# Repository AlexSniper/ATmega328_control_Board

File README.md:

# ATmega328 Control Board

Custom embedded control board based on the ATmega328PU microcontroller, designed in KiCad and compatible with Arduino firmware.

## Prototype Board

## Assembly

## Testing Setup

## Clock Verification
External 16 MHz crystal verified using oscilloscope.

## Power Testing
Board powered and tested using laboratory power supply.

## LCD Interface Test
16×2 LCD connected to the ATmega328 board to verify digital IO functionality and firmware operation.
Display output confirms correct microcontroller operation.

.png)

### Features
- ATmega328PU microcontroller
- 16 MHz external crystal
- MOSFET output drivers
- Screw terminal IO
- USB programming interface
- External power supply

## Repository structure

hardware – KiCad PCB design  
firmware – Arduino firmware  
gerbers – manufacturing files  
bom – bill of materials  
docs – schematic PDF  
images – hardware prototype photos

## Hardware validation

Clock oscillator verified with oscilloscope.

Board powered and tested using laboratory power supply.

## Hardware Revision History

v0.1 – Initial prototype PCB  
v0.2 – Improved routing and component placement  
v0.3 – Stable prototype, validated clock and power supply

## Author

AL Robotics

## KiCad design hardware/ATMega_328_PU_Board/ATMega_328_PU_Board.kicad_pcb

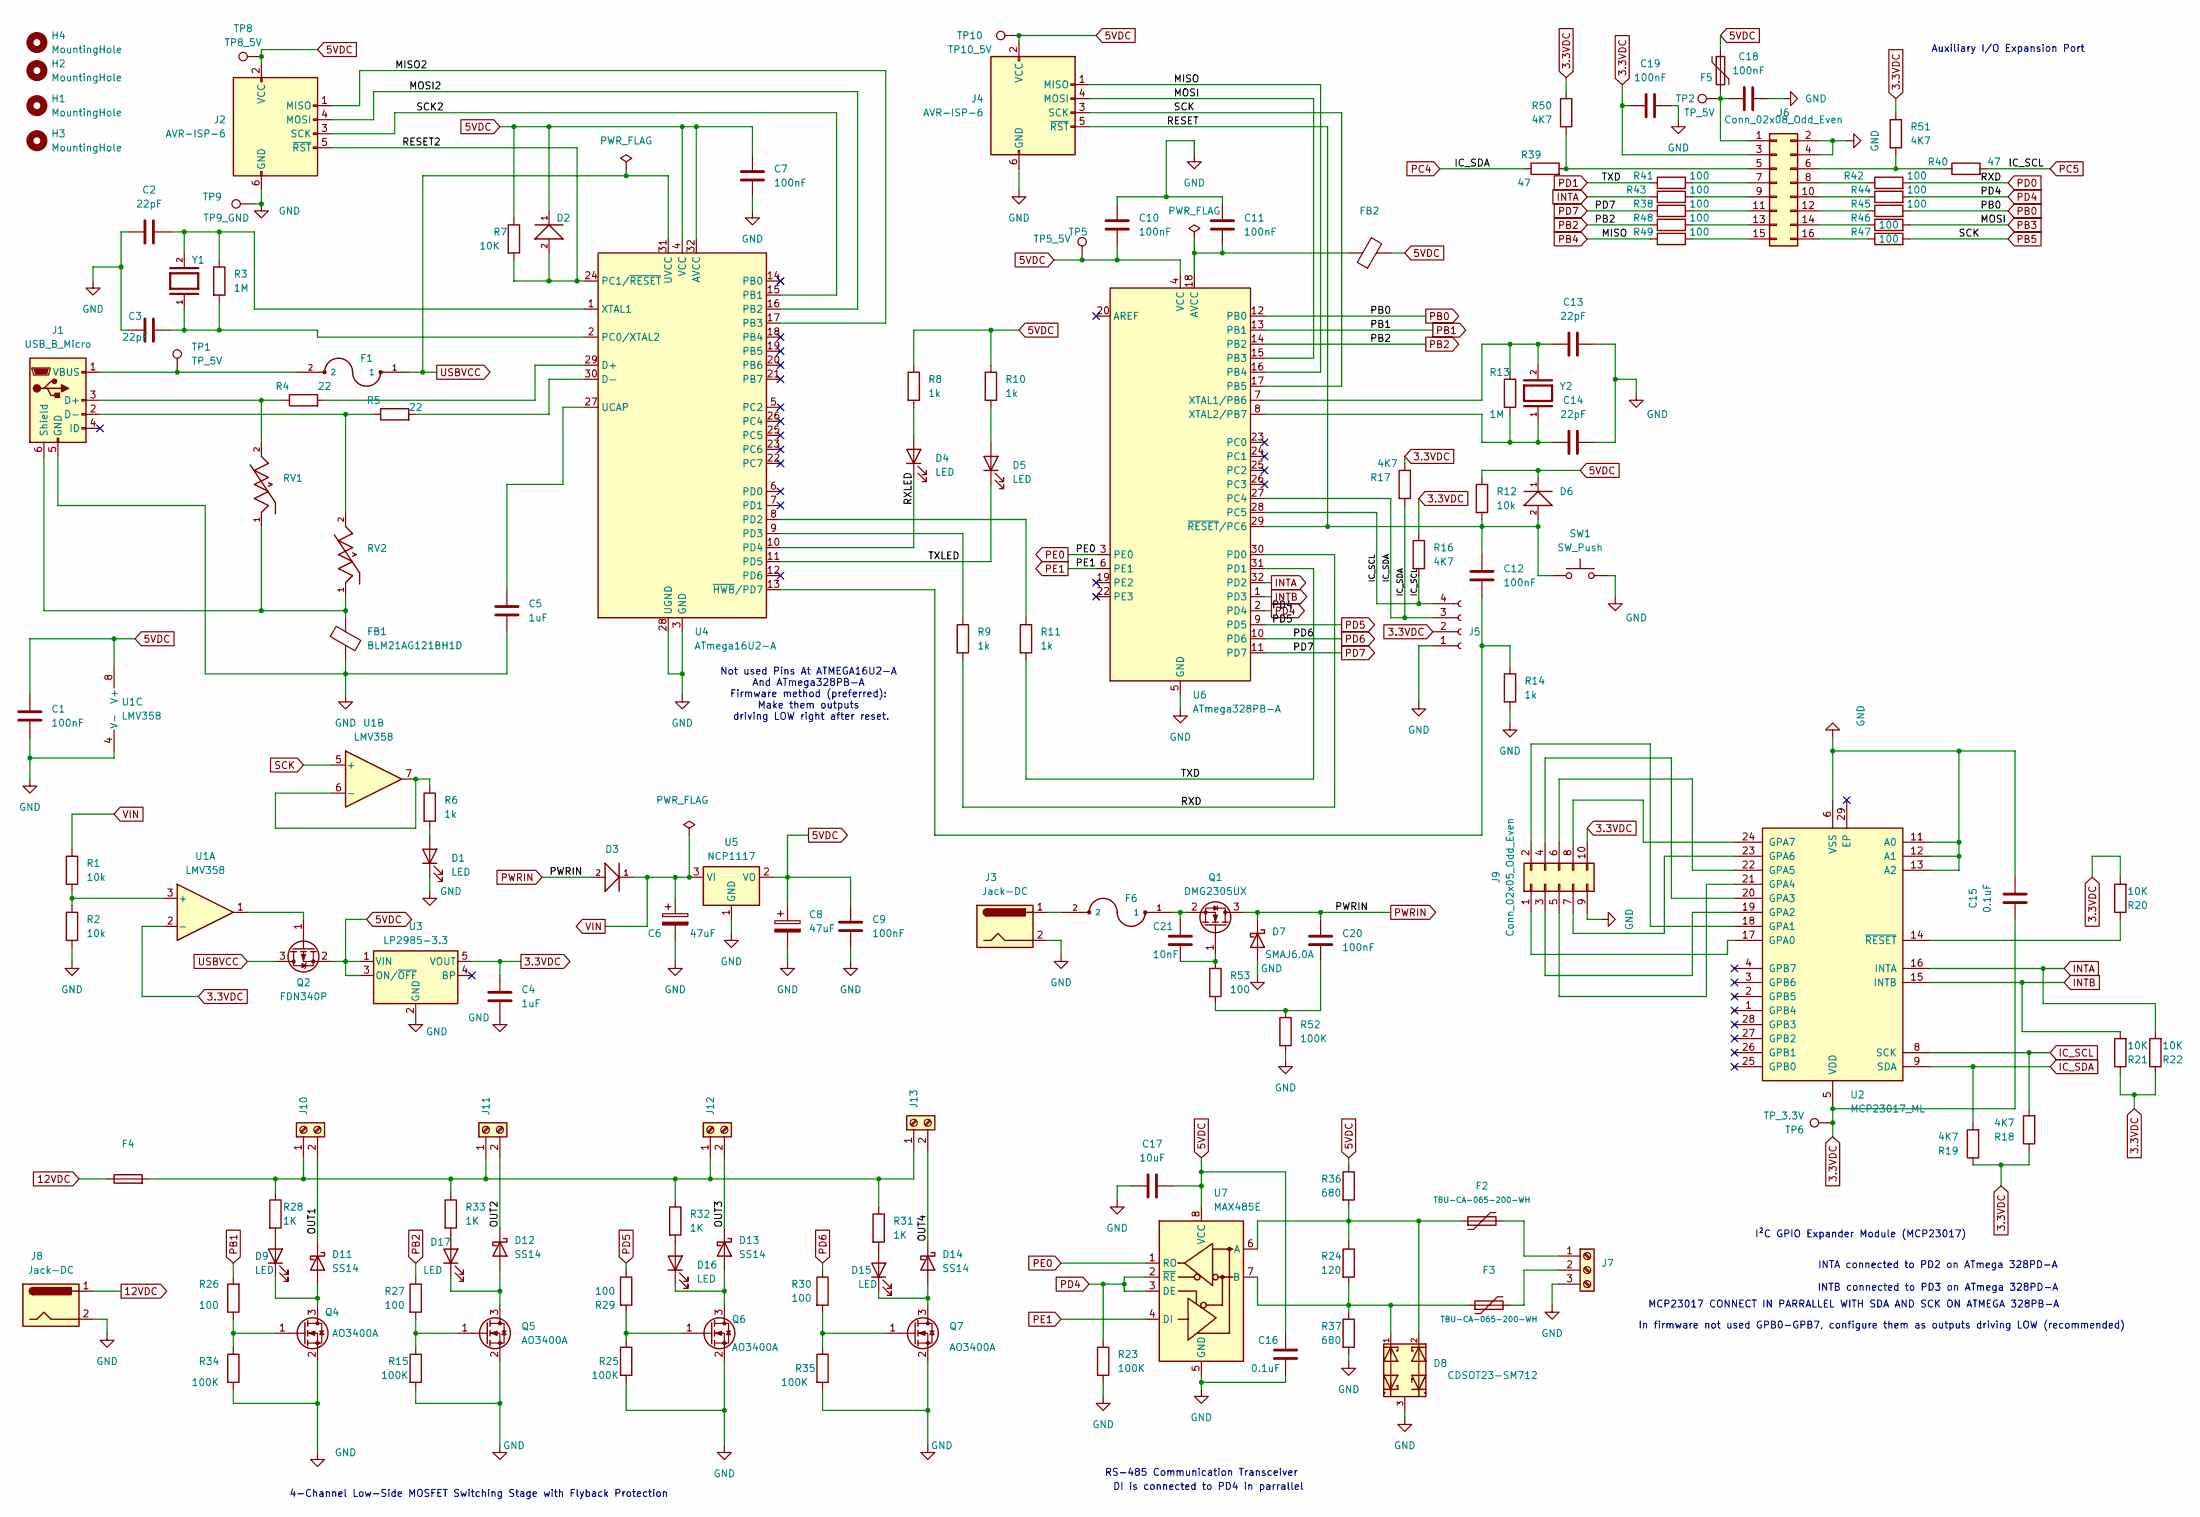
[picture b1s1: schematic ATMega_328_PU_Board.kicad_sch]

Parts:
C1, C7, C9, C10, C11, C12, C18, C19, C20: 100nF; C_0805_2012Metric_Pad1.18x1.45mm_HandSolder
C2, C3, C13, C14: 22pF; C_0805_2012Metric_Pad1.18x1.45mm_HandSolder
C4, C5: 1uF; C_0805_2012Metric_Pad1.18x1.45mm_HandSolder
C6, C8: 47uF; C_Radial_D5.0mm_H11.0mm_P2.00mm
C15, C16: 0.1uF; C_0805_2012Metric_Pad1.18x1.45mm_HandSolder
C17: 10uF; C_0805_2012Metric_Pad1.18x1.45mm_HandSolder
C21: 10nF; C_0805_2012Metric_Pad1.18x1.45mm_HandSolder
D1, D4, D5, D9, D15, D16, D17: LED; D_0805_2012Metric_Pad1.15x1.40mm_HandSolder
D2, D6: MMSD4148T1G; D_SOD-123; MPN CD1206-S01575
D3: B5819W; D_SOD-123; MPN CD1206-S01575
D7: SMAJ6.0A; D_SMA
D8: CDSOT23-SM712; SOT-23
D11, D12, D13, D14: SS14; D_SMA
F1, F6: MF-MSMF050-2; Fuse_1812_4532Metric_Pad1.30x3.40mm_HandSolder
F2, F3: TBU-CA-065-200-WH; Fuse_Bourns_TBU-CA
F4: 0805L200SLTHYR; Fuse_0805_2012Metric_Pad1.15x1.40mm_HandSolder
F5: PTSAHT120624V050; Fuse_1206_3216Metric_Pad1.42x1.75mm_HandSolder
FB1, FB2: BLM21AG121BH1D; L_0805_2012Metric_Pad1.05x1.20mm_HandSolder
H1, H2, H3, H4: MountingHole; MountingHole_3.2mm_M3
J1: USB_B_Micro; USB_Micro-B_Molex-105017-0001
J2, J4: AVR-ISP-6; PinHeader_2x03_P2.54mm_Vertical
J3, J8: Jack-DC; BarrelJack_CUI_PJ-102AH_Horizontal
J5: Conn_01x04_Socket; JST_PH_B4B-PH-K_1x04_P2.00mm_Vertical
J6: Conn_02x08_Odd_Even; PinHeader_2x08_P2.54mm_Vertical
J7: Screw_Terminal_01x03; TerminalBlock_Phoenix_MKDS-1,5-3-5.08_1x03_P5.08mm_Horizont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
J9: Conn_02x05_Odd_Even; PinHeader_2x05_P2.54mm_Vertical
J10, J11, J12, J13: Screw_Terminal_01x02; TerminalBlock_Phoenix_MKDS-1,5-2-5.08_1x02_P5.08mm_Horizont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
Q1: DMG2305UX; SOT-23
Q2: FDN340P; SOT-23
Q4, Q5, Q6, Q7: AO3400A; SOT-23
R1, R2, R12: 10k; R_0805_2012Metric_Pad1.20x1.40mm_HandSolder
R3, R13: 1M; R_0805_2012Metric_Pad1.20x1.40mm_HandSolder
R4, R5: 22; R_0805_2012Metric_Pad1.20x1.40mm_HandSolder
R6, R8, R9, R10, R11, R14: 1k; R_0805_2012Metric_Pad1.20x1.40mm_HandSolder
R7, R20, R21, R22: 10K; R_0805_2012Metric_Pad1.20x1.40mm_HandSolder
R15, R23, R25, R34, R35, R52: 100K; R_0805_2012Metric_Pad1.20x1.40mm_HandSolder
R16, R17, R18, R19, R50, R51: 4K7; R_0805_2012Metric_Pad1.20x1.40mm_HandSolder
R24: 120; R_0805_2012Metric_Pad1.20x1.40mm_HandSolder
R26, R27, R29, R30, R38, R41, R42, R43, R44, R45, R46, R47, R48, R49, R53: 100; R_0805_2012Metric_Pad1.20x1.40mm_HandSolder
R28, R31, R32, R33: 1K; R_0805_2012Metric_Pad1.20x1.40mm_HandSolder
R36, R37: 680; R_0805_2012Metric_Pad1.20x1.40mm_HandSolder
R39, R40: 47; R_0805_2012Metric_Pad1.20x1.40mm_HandSolder
RV1, RV2: CG0603MLC-05E; C_0603_1608Metric_Pad1.08x0.95mm_HandSolder; PARTREV E
SW1: SW_Push; SW_Tactile_SPST_NO_Straight_CK_PTS636Sx25SMTRLFS
TP1, TP2: TP_5V; TestPoint_Pad_1.5x1.5mm
TP5: TP5_5V; TestPoint_Pad_1.5x1.5mm
TP6: TP_3.3V; TestPoint_Pad_1.5x1.5mm
TP8: TP8_5V; TestPoint_Pad_1.5x1.5mm
TP9: TP9_GND; TestPoint_Pad_1.5x1.5mm
TP10: TP10_5V; TestPoint_Pad_1.5x1.5mm
U1: LMV358; SOIC-8_3.9x4.9mm_P1.27mm
U2: MCP23017_ML; QFN-28-1EP_6x6mm_P0.65mm_EP4.25x4.25mm
U3: LP2985-3.3; SOT-23-5
U4: ATmega16U2-A; TQFP-32_7x7mm_P0.8mm
U5: NCP1117; SOT-223-3_TabPin2
U6: ATmega328PB-A; TQFP-32_7x7mm_P0.8mm
U7: MAX485E; SOIC-8_3.9x4.9mm_P1.27mm
Y1, Y2: ABLS-16.000MHZ-D-4-T; Crystal_SMD_HC49-SD_HandSoldering; PARTREV 02.16.2021

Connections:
3.3VDC: C4.1, C15.1, C19.2, J5.2, J6.3, J9.10, R16.1, R17.1, R18.1, R19.1, R20.2, R21.1, R22.1, R50.1, R51.1, TP6.1, U1.2 (-), U2.5 (VDD), U3.5 (VOUT)
5VDC: C1.1, C7.1, C8.1, C9.1, C10.2, C16.1, C17.2, D2.1, D6.1, F5.1, FB2.2, J2.2 (VCC), J4.2 (VCC), Q2.2 (S), R7.1, R8.1, R10.1, R12.1, R36.1, TP5.1, TP8.1, TP10.1, U1.8 (V+), U3.1 (VIN), U3.3 (ON/~OFF), U4.4 (VCC), U4.32 (AVCC), U5.2 (VO), U6.4 (VCC), U7.8 (VCC)
12VDC: F4.1, J8.1
/MISO2: J2.1 (MISO), U4.17 (PB3)
/MOSI2: J2.4 (MOSI), U4.16 (PB2)
/OUT1: D11.1 (K), J10.2
/OUT2: D12.1 (K), J11.2
/OUT3: D13.1 (K), J12.2
/OUT4: D14.1 (K), J13.2
/RESET: C12.1, D6.2, J4.5 (~RST), R12.2, SW1.1, U6.29 (~RESET/PC6)
/RESET2: D2.2, J2.5 (~RST), R7.2, U4.24 (PC1/~RESET)
/RXLED: D4.1 (K), U4.10 (PD4)
/SCK2: J2.3 (SCK), U4.15 (PB1)
/TXLED: D5.1 (K), U4.11 (PD5)
GND: C1.2, C2.1, C3.1, C4.2, C5.2, C6.2, C7.2, C8.2, C9.2, C10.1, C11.1, C13.2, C14.2, C15.2, C16.2, C17.1, C18.2, C19.1, D1.1 (K), D7.2 (A), D8.3, FB1.2, J1.5 (GND), J2.6 (GND), J3.2, J4.6 (GND), J5.1, J6.2, J6.4, J7.3, J8.2, J9.9, Q4.2 (S), Q5.2 (S), Q6.2 (S), Q7.2 (S), R2.2, R14.2, R15.2, R23.2, R25.2, R34.2, R35.2, R37.2, R52.2, SW1.2, TP9.1, U1.4 (V-), U2.6 (VSS), U2.11 (A0), U2.12 (A1), U2.13 (A2), U3.2 (GND), U4.3 (GND), U4.28 (UGND), U5.1 (GND), U6.5 (GND), U6.21 (GND), U7.5 (GND)
IC_SCL: J5.4, R16.2, R18.2, R40.2, U2.8 (SCK), U6.28 (PC5)
IC_SDA: J5.3, R17.2, R19.2, R39.1, U2.9 (SDA), U6.27 (PC4)
INTA: R22.2, R43.1, U2.16 (INTA), U6.32 (PD2)
INTB: R21.2, U2.15 (INTB), U6.1 (PD3)
unnamed: C20.2, R52.1, R53.2
unnamed: D1.2 (A), R6.2
unnamed: D4.2 (A), R8.2
unnamed: D5.2 (A), R10.2
unnamed: D9.2 (A), R28.2
unnamed: D9.1 (K), D11.2 (A), Q4.3 (D)
unnamed: D12.2 (A), D17.1 (K), Q5.3 (D)
unnamed: D13.2 (A), D16.1 (K), Q6.3 (D)
unnamed: D14.2 (A), D15.1 (K), Q7.3 (D)
unnamed: D15.2 (A), R31.2
unnamed: D16.2 (A), R32.2
unnamed: D17.2 (A), R33.2
unnamed: F6.2, J3.1
unnamed: J1.3 (D+), R4.1, RV1.2
unnamed: J1.2 (D-), R5.1, RV2.2
unnamed: FB1.1, J1.6 (Shield), RV1.1, RV2.1
unnamed: F1.2, J1.1 (VBUS), TP1.1
unnamed: C18.1, F5.2, J6.1, TP2.1
unnamed: J6.5, R39.2, R50.2
unnamed: J6.6, R40.1, R51.2
unnamed: J6.7, R41.2
unnamed: J6.8, R42.1
unnamed: J6.9, R43.2
unnamed: J6.10, R44.1
unnamed: J6.11, R38.2
unnamed: J6.12, R45.1
unnamed: J6.13, R48.2
unnamed: J6.14, R46.1
unnamed: J6.15, R49.2
unnamed: J6.16, R47.1
unnamed: F2.3, J7.1
unnamed: F3.3, J7.2
unnamed: J9.1, U2.17 (GPA0)
unnamed: J9.2, U2.18 (GPA1)
unnamed: J9.3, U2.19 (GPA2)
unnamed: J9.4, U2.20 (GPA3)
unnamed: J9.5, U2.21 (GPA4)
unnamed: J9.6, U2.22 (GPA5)
unnamed: J9.7, U2.23 (GPA6)
unnamed: J9.8, U2.24 (GPA7)
unnamed: F4.2, J10.1, J11.1, J12.1, J13.1, R28.1, R31.1, R32.1, R33.1
unnamed: C21.2, Q1.1 (G), R53.1
unnamed: C21.1, F6.1, Q1.2 (S)
unnamed: Q2.1 (G), U1.1
unnamed: Q4.1 (G), R26.1, R34.1
unnamed: Q5.1 (G), R15.1, R27.2
unnamed: Q6.1 (G), R25.1, R29.2
unnamed: Q7.1 (G), R30.2, R35.1
unnamed: R1.2, R2.1, U1.3 (+)
unnamed: R6.1, U1.6 (-), U1.7
unnamed: R20.1, U2.14 (~RESET)
unnamed: R4.2, U4.29 (D+)
unnamed: R5.2, U4.30 (D-)
unnamed: C3.2, R3.2, U4.2 (PC0/XTAL2), Y1.1
unnamed: R11.1, U4.8 (PD2)
unnamed: R9.1, U4.9 (PD3)
unnamed: C5.1, U4.27 (UCAP)
unnamed: C2.2, R3.1, U4.1 (XTAL1), Y1.2
unnamed: C12.2, R14.1, U4.13 (~HWB/PD7)
unnamed: C11.2, FB2.1, U6.18 (AVCC)
unnamed: C13.1, R13.1, U6.7 (XTAL1/PB6), Y2.2
unnamed: C14.1, R13.2, U6.8 (XTAL2/PB7), Y2.1
unnamed: D8.2, F2.1, R24.1, R36.2, U7.6 (A)
unnamed: D8.1, F3.1, R24.2, R37.1, U7.7 (B)
PB0: R45.2, U6.12 (PB0)
PB1: R26.2, U6.13 (PB1)
PB2: R27.1, R48.1, U6.14 (PB2)
PB3: J4.4 (MOSI), R46.2, U6.15 (PB3)
PB4: J4.1 (MISO), R49.1, U6.16 (PB4)
PB5: J4.3 (SCK), R47.2, U1.5 (+), U6.17 (PB5)
PD0: R9.2, R42.2, U6.30 (PD0)
PD1: R11.2, R41.1, U6.31 (PD1)
PD5: R29.1, U6.9 (PD5)
PD6: R30.1, U6.10 (PD6)
PD7: R38.1, U6.11 (PD7)
PE0: U6.3 (PE0), U7.1 (RO)
PE1: U6.6 (PE1), U7.4 (DI)
PWRIN: C20.1, D3.2, D7.1 (K), Q1.3 (D)
USBVCC: F1.1, Q2.3 (D), U4.31 (UVCC)
VIN: C6.1, D3.1, R1.1, U5.3 (VI)

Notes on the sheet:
Not used Pins At ATMEGA16U2-A And ATmega328PB-A Firmware method (preferred): Make them outputs driving LOW right after reset.
Auxiliary I/O Expansion Port
In firmware not used GPB0-GPB7, configure them as outputs driving LOW (recommended)
4-Channel Low-Side MOSFET Switching Stage with Flyback Protection
RS-485 Communication Transceiver
MCP23017 CONNECT IN PARRALLEL WITH SDA AND SCK ON ATMEGA 328PB-A
DI is connected to PD4 in parrallel
I²C GPIO Expander Module (MCP23017)
INTA connected to PD2 on ATmega 328PD-A INTB connected to PD3 on ATmega 328PD-A

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
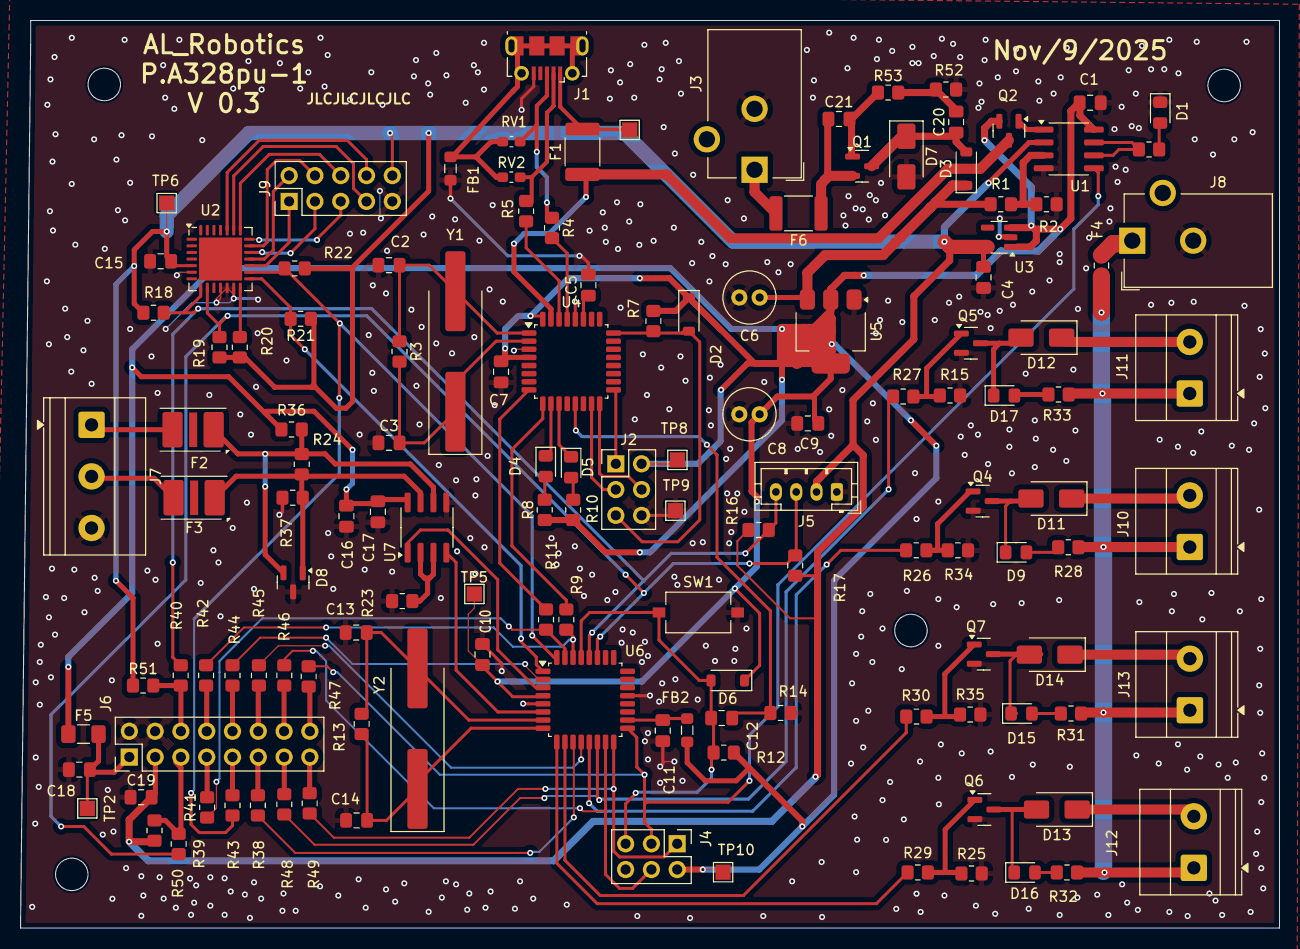
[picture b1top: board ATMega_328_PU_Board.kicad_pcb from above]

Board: 4 copper layers, 124.0 x 89.4 mm, 140 parts (0 on the bottom side), 101 nets.

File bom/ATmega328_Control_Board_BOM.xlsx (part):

Reference | Qty | Value | MANUFACTURER # | Link | Footprint
C1,C7,C9,C10,C11,C12,C18,C19,C20 | 9.0 | 100nF | KAF21BR71H104JM | https://www.mouser.ca/ProductDetail/KYOCERA-AVX/KAF21BR71H10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 | Capacitor_SMD:C_0805_2012Metric_Pad1.18x1.45mm_HandSolder
C2,C3,C13,C14 | 4.0 | 22pF | C0805C220M5HACTU | https://www.mouser.ca/ProductDetail/KEMET/C0805C220M5HACTU?q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 | Capacitor_SMD:C_0805_2012Metric_Pad1.18x1.45mm_HandSolder
C4,C5 | 2.0 | 1uF | CL21B105KBFNNNE | https://www.mouser.ca/ProductDetail/Samsung-Electro-Mechanic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 | Capacitor_SMD:C_0805_2012Metric_Pad1.18x1.45mm_HandSolder
C6,C8 | 2.0 | 47uF | 8.60020472006E11 | https://www.mouser.ca/ProductDetail/Wurth-Elektronik/8600204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 | Capacitor_THT:C_Radial_D5.0mm_H11.0mm_P2.00mm
C15,C16 | 2.0 | 0.1uF | KAF21BR71H104JM | https://www.mouser.ca/ProductDetail/KYOCERA-AVX/KAF21BR71H10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 | Capacitor_SMD:C_0805_2012Metric_Pad1.18x1.45mm_HandSolder
C17 | 1.0 | 10uF | CL21A106KAYNNNE | https://www.mouser.ca/ProductDetail/Samsung-Electro-Mechanic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 | Capacitor_SMD:C_0805_2012Metric_Pad1.18x1.45mm_HandSolder
C21 | 1.0 | 10nF | KAF21BR71H103KT | https://www.mouser.ca/ProductDetail/KYOCERA-AVX/KAF21BR71H10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 | Capacitor_SMD:C_0805_2012Metric_Pad1.18x1.45mm_HandSolder
D1,D4,D5,D9,D15,D16,D17 | 7.0 | LED | LTST-C170GKT | https://www.mouser.ca/ProductDetail/LITEON/LTST-C170GKT?qs=s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 | Diode_SMD:D_0805_2012Metric_Pad1.15x1.40mm_HandSolder
D2,D6 | 2.0 | MMSD4148T1G | MMSD4148T1G | https://www.digikey.ca/en/products/detail/onsemi/MMSD4148T1G/919705 | Diode_SMD:D_SOD-123
D3 | 1.0 | B5819W | B5819W | https://www.digikey.ca/en/products/detail/good-ark-semicondu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 | Diode_SMD:D_SOD-123
D7 | 1.0 | SMAJ6.0A | SMAJ6.0A | https://www.digikey.ca/en/products/detail/littelfuse-inc/SMA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 | Diode_SMD:D_SMA
D8 | 1.0 | CDSOT23-SM712 | CDSOT23-SM712 | https://www.digikey.ca/en/products/detail/bourns-inc/cdsot23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 | Package_TO_SOT_SMD:SOT-23
D11,D12,D13,D14 | 4.0 | SS14 | SS14 | https://www.mouser.ca/ProductDetail/onsemi-Fairchild/SS14?qs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 | Diode_SMD:D_SMA
F1,F6 | 2.0 | MF-MSMF050-2 | MF-MSMF050-2 | https://www.digikey.ca/en/products/detail/bourns-inc/MF-MSMF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 | Fuse:Fuse_1812_4532Metric_Pad1.30x3.40mm_HandSolder
F2,F3 | 2.0 | TBU-CA-065-200-WH | TBU-CA-065-200-WH | https://www.mouser.ca/ProductDetail/Bourns/TBU-CA065-200-WH?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 | Fuse:Fuse_Bourns_TBU-CA
F4 | 1.0 | 0805L200SLTHYR | 0805L200SLTHYR | https://www.digikey.ca/en/products/detail/littelfuse-inc/080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 | Fuse:Fuse_0805_2012Metric_Pad1.15x1.40mm_HandSolder
F5 | 1.0 | PTSAHT120624V050 | PTSAHT120624V050 | https://www.digikey.ca/en/products/detail/eaton-electronics-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 | Fuse:Fuse_1206_3216Metric_Pad1.42x1.75mm_HandSolder
FB1,FB2 | 2.0 | BLM21AG121BH1D | BLM21AG121BH1D | https://www.mouser.ca/ProductDetail/Murata-Electronics/BLM21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 | Inductor_SMD:L_0805_2012Metric_Pad1.05x1.20mm_HandSolder
H1,H2,H3,H4 | 4.0 | MountingHole |  |  | MountingHole:MountingHole_3.2mm_M3
J1 | 1.0 | USB_B_Micro | 1.050170001E9 | https://www.digikey.ca/en/products/detail/molex/1050170001/2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 | Connector_USB:USB_Micro-B_Molex-105017-0001
J2,J4 | 2.0 | AVR-ISP-6 | M20-9980346 | https://www.digikey.ca/en/products/detail/harwin-inc/M20-998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 | Connector_PinHeader_2.54mm:PinHeader_2x03_P2.54mm_Vertical
J3,J8 | 2.0 | Jack-DC | PJ-102AH | https://www.digikey.ca/en/products/detail/same-sky-formerly-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 | Connector_BarrelJack:BarrelJack_CUI_PJ-102AH_Horizontal
J5 | 1.0 | Conn_01x04_Socket | B4B-PH-K | https://www.digikey.ca/en/products/detail/jst-sales-america-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 | Connector_JST:JST_PH_B4B-PH-K_1x04_P2.00mm_Vertical
J6 | 1.0 | Conn_02x08_Odd_Even | 10129381-916001BLF | https://www.mouser.ca/ProductDetail/Amphenol-FCI/10129381-91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 | Connector_PinHeader_2.54mm:PinHeader_2x08_P2.54mm_Vertical
J7 | 1.0 | Screw_Terminal_01x03 | TB006-508-03BE | https://www.digikey.ca/en/products/detail/same-sky-formerly-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 | TerminalBlock_Phoenix:TerminalBlock_Phoenix_MKDS-1,5-3-5.08_1x03_P5.08mm_Horizo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
J9 | 1.0 | Conn_02x05_Odd_Even | 6.1301021121E10 | https://www.digikey.ca/en/products/detail/w%C3%BCrth-elektro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 | Connector_PinHeader_2.54mm:PinHeader_2x05_P2.54mm_Vertical
J10,J11,J12,J13 | 4.0 | Screw_Terminal_01x02 | TB006-508-02BE | https://www.digikey.ca/en/products/detail/same-sky-formerly-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 | TerminalBlock_Phoenix:TerminalBlock_Phoenix_MKDS-1,5-2-5.08_1x02_P5.08mm_Horizo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
Q1 | 1.0 | DMG2305UX | DMG2305UX-7 | https://www.digikey.ca/en/products/detail/diodes-incorporate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 | Package_TO_SOT_SMD:SOT-23
Q2 | 1.0 | FDN340P | FDN340P | https://www.digikey.ca/en/products/detail/umw/FDN340P/16705911 | Package_TO_SOT_SMD:SOT-23
Q4,Q5,Q6,Q7 | 4.0 | AO3400A | AO3400A | https://www.digikey.ca/en/products/detail/alpha-omega-semico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 | Package_TO_SOT_SMD:SOT-23
R1,R2,R12 | 3.0 | 10k | CR0805-JW-103ELF | https://www.mouser.ca/ProductDetail/Bourns/CR0805-JW-103ELF?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 | Resistor_SMD:R_0805_2012Metric_Pad1.20x1.40mm_HandSolder
R3,R13 | 2.0 | 1M | CRGCQ0805F1M0 | https://www.mouser.ca/ProductDetail/TE-Connectivity-Holswort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 | Resistor_SMD:R_0805_2012Metric_Pad1.20x1.40mm_HandSolder
R4,R5 | 2.0 | 22.0 | RK73H2ATTDD22R0F | https://www.mouser.ca/ProductDetail/KOA-Speer/RK73H2ATTDD22R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 | Resistor_SMD:R_0805_2012Metric_Pad1.20x1.40mm_HandSolder
R6,R8,R9,R10,R11,R14 | 6.0 | 1k | CRCW08051K00FKTAHP | https://www.mouser.ca/ProductDetail/Vishay/CRCW08051K00FKTAH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 | Resistor_SMD:R_0805_2012Metric_Pad1.20x1.40mm_HandSolder
R7,R20,R21,R22 | 4.0 | 10K | CR0805-JW-103ELF | https://www.mouser.ca/ProductDetail/Bourns/CR0805-JW-103ELF?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 | Resistor_SMD:R_0805_2012Metric_Pad1.20x1.40mm_HandSolder
R15,R23,R25,R34,R35,R52 | 6.0 | 100K | RK73H2ATTE1003F | https://www.mouser.ca/ProductDetail/KOA-Speer/RK73H2ATTE1003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 | Resistor_SMD:R_0805_2012Metric_Pad1.20x1.40mm_HandSolder
R16,R17,R18,R19,R50,R51 | 6.0 | 4K7 | CRCW08054K70FKEAC | https://www.digikey.ca/en/products/detail/vishay-dale/CRCW08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 | Resistor_SMD:R_0805_2012Metric_Pad1.20x1.40mm_HandSolder
R24 | 1.0 | 120.0 | RMCF0805FT120R | https://www.digikey.ca/en/products/detail/stackpole-electron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 | Resistor_SMD:R_0805_2012Metric_Pad1.20x1.40mm_HandSolder
R26,R27,R29,R30,R38,R41,R42,R43,R44,R45,R46,R47,R48,R49,R53 | 15.0 | 100.0 | ERA-6AEB101V | https://www.digikey.ca/en/products/detail/panasonic-electron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 | Resistor_SMD:R_0805_2012Metric_Pad1.20x1.40mm_HandSolder
R28,R31,R32,R33 | 4.0 | 1K | CRCW08051K00FKEA | https://www.digikey.ca/en/products/detail/vishay-dale/CRCW08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 | Resistor_SMD:R_0805_2012Metric_Pad1.20x1.40mm_HandSolder
R36,R37 | 2.0 | 680.0 | ERJ-6GEYJ681V | https://www.digikey.ca/en/products/detail/panasonic-electron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 | Resistor_SMD:R_0805_2012Metric_Pad1.20x1.40mm_HandSolder
R39,R40 | 2.0 | 47.0 | RMCF0805JT47R0 | https://www.digikey.ca/en/products/detail/stackpole-electron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 | Resistor_SMD:R_0805_2012Metric_Pad1.20x1.40mm_HandSolder
RV1,RV2 | 2.0 | CG0603MLC-05E | CG0603MLC-05E | https://www.digikey.ca/en/products/detail/bourns-inc/CG0603M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 | Capacitor_SMD:C_0603_1608Metric_Pad1.08x0.95mm_HandSolder
SW1 | 1.0 | SW_Push | PTS636 SP50 SMTR LFS | https://www.mouser.ca/ProductDetail/CK/PTS636SP50SMTR-LFS?qs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 | Button_Switch_SMD:SW_Tactile_SPST_NO_Straight_CK_PTS636Sx25SMTRLFS
TP1,TP2 | 2.0 | TP_5V |  |  | TestPoint:TestPoint_Pad_1.5x1.5mm
TP5 | 1.0 | TP5_5V |  |  | TestPoint:TestPoint_Pad_1.5x1.5mm
TP6 | 1.0 | TP_3.3V |  |  | TestPoint:TestPoint_Pad_1.5x1.5mm
TP8 | 1.0 | TP8_5V |  |  | TestPoint:TestPoint_Pad_1.5x1.5mm
TP9 | 1.0 | TP9_GND |  |  | TestPoint:TestPoint_Pad_1.5x1.5mm
TP10 | 1.0 | TP10_5V |  |  | TestPoint:TestPoint_Pad_1.5x1.5mm
U1 | 1.0 | LMV358 | LMV358IDR | https://www.digikey.ca/en/products/detail/texas-instruments/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 | Package_SO:SOIC-8_3.9x4.9mm_P1.27mm
U2 | 1.0 | MCP23017_ML | MCP23017-E/ML | https://www.digikey.ca/en/products/detail/microchip-technolo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 | Package_DFN_QFN:QFN-28-1EP_6x6mm_P0.65mm_EP4.25x4.25mm
U3 | 1.0 | LP2985-3.3 | LP2985-33DBVR | https://www.digikey.ca/en/products/detail/texas-instruments/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 | Package_TO_SOT_SMD:SOT-23-5
U4 | 1.0 | ATmega16U2-A | ATMEGA16U2-AU | https://www.digikey.ca/en/products/detail/microchip-technolo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 | Package_QFP:TQFP-32_7x7mm_P0.8mm
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
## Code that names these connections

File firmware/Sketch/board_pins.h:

#pragma once
#include <Arduino.h>

// ------------------------------------------------------------
// Al_Robotics — ATmega328PB @ 16 MHz (MiniCore pin mapping)
// ------------------------------------------------------------
// UART0 (PD0/PD1) <-> ATmega16U2 USB bridge
constexpr uint8_t PIN_RX0 = 0;    // PD0 (USART0 RXD)
constexpr uint8_t PIN_TX0 = 1;    // PD1 (USART0 TXD)

// I2C bus (Wire)
constexpr uint8_t PIN_SDA = A4;   // PC4 (SDA)
constexpr uint8_t PIN_SCL = A5;   // PC5 (SCL)

// MCP23017 interrupt lines -> ATmega external interrupts
constexpr uint8_t PIN_INT_A = 2;  // PD2 / INT0  (MCP INTA)
constexpr uint8_t PIN_INT_B = 3;  // PD3 / INT1  (MCP INTB)

// RS-485 enable control (DE and /RE are tied together on the PCB)
constexpr uint8_t PIN_RS485_DE_RE = 4;  // PD4 drives MAX485 pins 2+3 (DE & /RE)

// ------------------------------------------------------------
// Notes (for reference, no defines needed here):
// * MAX485 DI  (pin 4)  -> ATmega328PB PE1 (USART1 TXD)  == Serial1 TX
// * MAX485 RO  (pin 1)  -> ATmega328PB PE0 (USART1 RXD)  == Serial1 RX
// * main.cpp selects UART at runtime (RS485UART 0|1), default = Serial1.
//
// Make sure MiniCore is set to ATmega328PB so Serial1 is available.
// ------------------------------------------------------------

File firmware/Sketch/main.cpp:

#include <Arduino.h>
#include <Wire.h>
#include <LiquidCrystal.h>
#include <Adafruit_MCP23X17.h>

// ---------------- LCD wiring (unchanged) ----------------
#define LCD_RS  8    // PB0
#define LCD_E   13   // PB5
#define LCD_D4  10   // PB2
#define LCD_D5  11   // PB3
#define LCD_D6  7    // PD7
#define LCD_D7  4    // PD4

LiquidCrystal lcd(LCD_RS, LCD_E, LCD_D4, LCD_D5, LCD_D6, LCD_D7);

// ---------------- MCP23017 ----------------
Adafruit_MCP23X17 mcp;
static constexpr uint8_t MCP_ADDR = 0x20;

// Button on MCP: GPA4 (J9-5) -> GND
static constexpr uint8_t BTN_PIN = 4;   // GPA4

// Motor OUT1 gate is PB1 -> Arduino D9
static constexpr uint8_t MOTOR_GATE_PIN = 9; // PB1 (controls Q4 / J10)

// Debounce (non-blocking)
static constexpr uint32_t DEBOUNCE_MS = 25;

bool motorOn = false;

// For edge detect + debounce
bool lastRaw = HIGH;       // raw button level (HIGH released, LOW pressed)
bool stable = HIGH;        // debounced stable level
uint32_t lastChangeMs = 0; // time raw last changed

void showStatus() {
  lcd.setCursor(0, 0);
  lcd.print("AL_Robotics     ");
  lcd.setCursor(0, 1);
  lcd.print("Motor: ");
  lcd.print(motorOn ? "ON " : "OFF");
  lcd.print("        ");
}

void setup() {
  delay(100);
  lcd.begin(16, 2);
  lcd.clear();
  lcd.print("AL_Robotics");
  lcd.setCursor(0, 1);
  lcd.print("Init...");

  Wire.begin();

  if (!mcp.begin_I2C(MCP_ADDR)) {
    lcd.clear();
    lcd.print("MCP23017 FAIL");
    lcd.setCursor(0, 1);
    lcd.print("Check I2C");
    while (true) {}
  }

  // Button input + enable MCP pull-up
  mcp.pinMode(BTN_PIN, INPUT);
  mcp.digitalWrite(BTN_PIN, HIGH); // enables pull-up

  // Recommended: GPB0..GPB7 outputs LOW
  for (uint8_t p = 8; p <= 15; p++) {
    mcp.pinMode(p, OUTPUT);
    mcp.digitalWrite(p, LOW);
  }

  // Motor gate
  pinMode(MOTOR_GATE_PIN, OUTPUT);
  digitalWrite(MOTOR_GATE_PIN, LOW);

  // Init debounce state
  stable = mcp.digitalRead(BTN_PIN);
  lastRaw = stable;
  lastChangeMs = millis();

  motorOn = false;
  showStatus();
}

void loop() {
  const uint32_t now = millis();

  // Read raw button
  const bool raw = mcp.digitalRead(BTN_PIN); // HIGH=release, LOW=pressed

  // Track raw changes
  if (raw != lastRaw) {
    lastRaw = raw;
    lastChangeMs = now;
  }

  // If raw has been stable long enough, accept as debounced state
  if ((now - lastChangeMs) >= DEBOUNCE_MS && raw != stable) {
    stable = raw;

    // Trigger on PRESS event (transition to LOW)
    if (stable == LOW) {
      motorOn = !motorOn;
      digitalWrite(MOTOR_GATE_PIN, motorOn ? HIGH : LOW);
      showStatus();
    }
  }
}

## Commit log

2026-03-15 Initial commit – ATmega328 control board project
    Added KiCad PCB design, firmware, BOM, Gerber files, documentation and prototype images.
2026-03-15 Add image to README for ATmega328 Control Board
2026-03-15 Update README with prototype and hardware validation images
    Added sections for assembly, testing setup, clock verification, and power testing.
2026-03-15 Update README with prototype and hardware validation images
2026-03-15 Update README with project description, images, and repository structure
    Updated project description for clarity and detail.
2026-03-15 Improve README documentation
    Added hardware revision history section to README.
2026-03-17 Add Power Testing section to README
    Added Power Testing section with image.
2026-03-17 Correct image references in README.md
    Fix image paths and formatting in README.
2026-03-17 Clean up README.md power testing section
    Remove duplicate power testing information and fix image syntax.
2026-03-17 Add LCD Interface Test section to README
    Added section for LCD interface testing to README.
2026-03-19 Add MIT License to the project
2026-03-28 Update copyright holder in LICENSE file
2026-03-28 Update README.md
    Remove author name from README
